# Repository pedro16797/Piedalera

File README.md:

# Piedalera

Firmware for a Raspberry Pi Pico MIDI pedalboard: 20 foot keys, two octave
buttons, a small OLED display and a 5-pin DIN MIDI output. Written in C on
the [Pico SDK](https://github.com/raspberrypi/pico-sdk).

- **Install it:** [setup guide](docs/setup-guide.md)
- **Play it:** [what each pedal does](docs/playing.md)
- **Change settings:** [configuration](docs/configuration.md)

The original MicroPython firmware is kept in [`legacy/`](legacy/) for
reference; this firmware supersedes it.

## Building

Needs the Pico SDK and an `arm-none-eabi` toolchain.

```sh
export PICO_SDK_PATH=/path/to/pico-sdk
cmake -B build -DPICO_BOARD=pico   # or pico_w, pico2, pico2_w
cmake --build build
```

Host tests (any C compiler):

```sh
cmake -S test -B build-test && cmake --build build-test && ctest --test-dir build-test
```

Display preview, rendered with the firmware's own drawing code; open
`build-preview/preview.html` afterwards:

```sh
cmake -S tools/preview -B build-preview
cmake --build build-preview --target preview-run
```

CI builds the firmware and default settings for all four boards on every
push to `master`; tagging `v*` publishes a release.

## Layout

| Path | Contents |
|------|----------|
| `src/` | Firmware ([architecture](docs/architecture.md)) |
| `test/` | Host tests |
| `tools/` | `config2uf2.py` (settings to UF2), `sprites.py` (PNG assets to C), `preview/` |
| `assets/` | Sprites for the splash, config icons and diagrams |
| `config/` | Default settings |
| `hardware/picorgano/` | KiCad board ([hardware](docs/hardware.md)) |
| `legacy/` | Original MicroPython firmware |

Plans are in the [roadmap](docs/roadmap.md).

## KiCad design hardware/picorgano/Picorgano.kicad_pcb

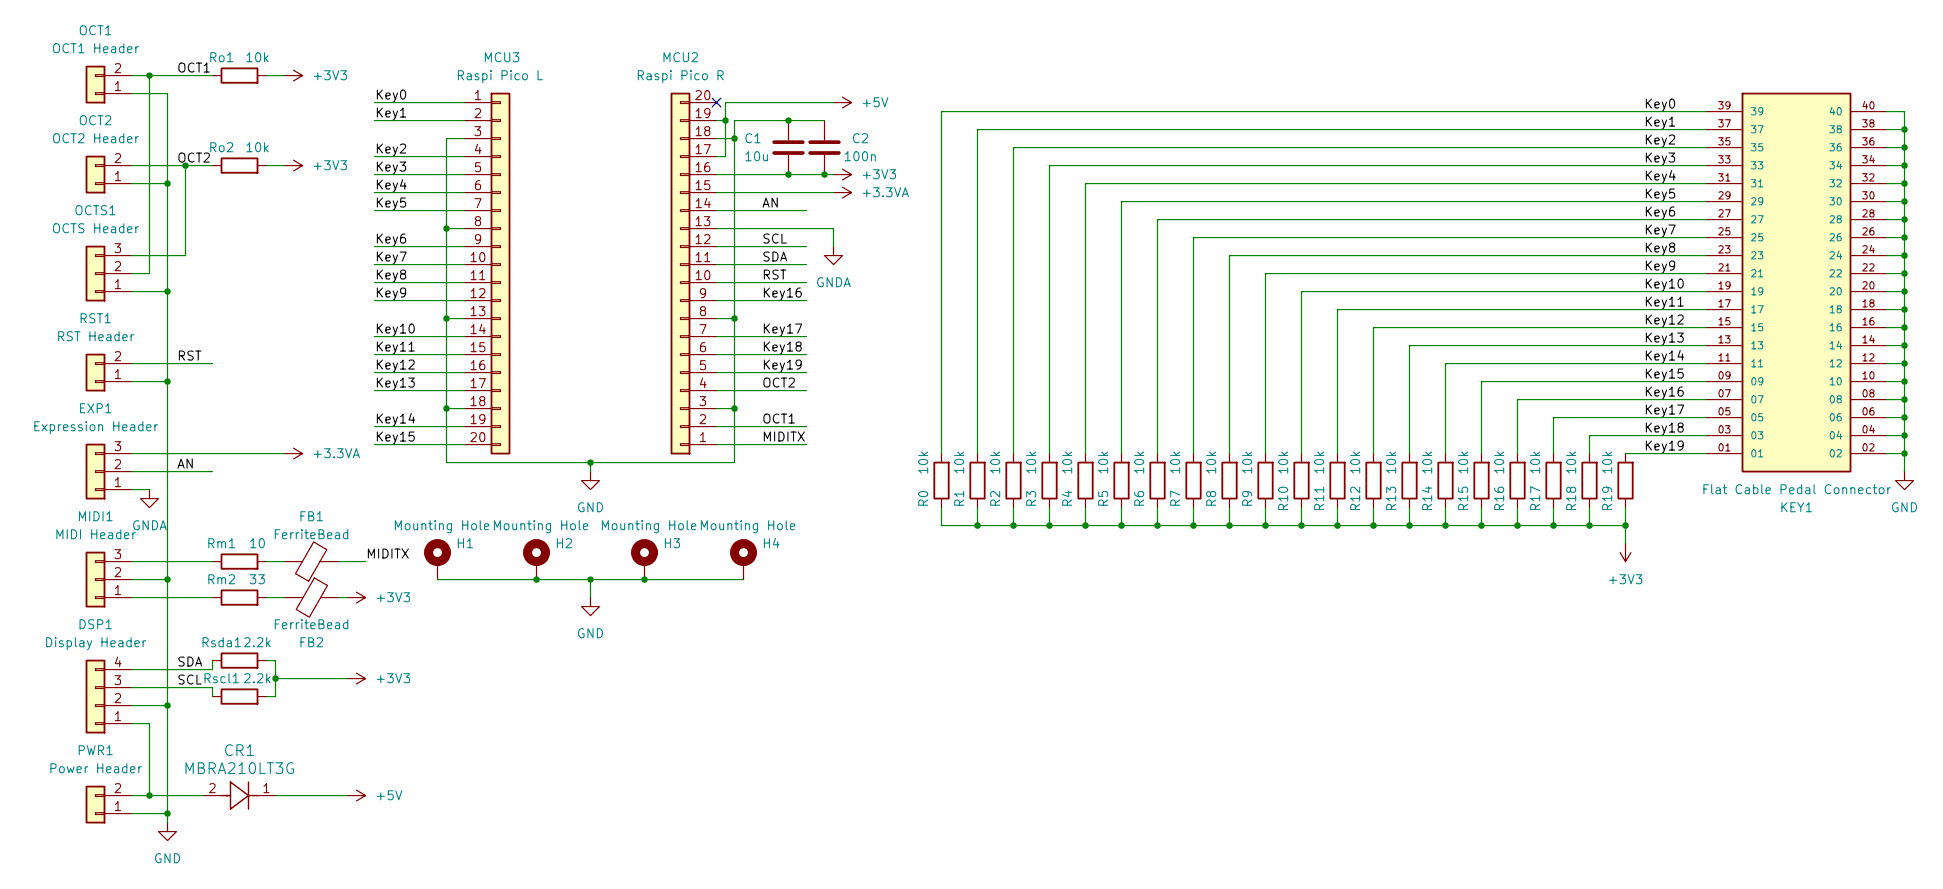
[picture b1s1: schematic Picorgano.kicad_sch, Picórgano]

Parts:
C1: 10u; CP_EIA-3216-10_Kemet-I_Pad1.58x1.35mm_HandSolder
C2: 100n; CP_EIA-3216-10_Kemet-I_Pad1.58x1.35mm_HandSolder
CR1: MBRA210LT3G; DIODE_SMA_4P32X2P6_ONS
DSP1: Display Header; JST_EH_B4B-EH-A_1x04_P2.50mm_Vertical
EXP1: Expression Header; JST_EH_B3B-EH-A_1x03_P2.50mm_Vertical
FB1, FB2: FerriteBead; R_1206_3216Metric
H1, H2, H3, H4: Mounting Hole; MountingHole_2.2mm_M2_DIN965_Pad
KEY1: Flat Cable Pedal Connector; SAMTEC_EHF-120-01-F-D; PARTREV R
MCU2: Raspi Pico R; PinSocket_1x20_P2.54mm_Vertical
MCU3: Raspi Pico L; PinSocket_1x20_P2.54mm_Vertical
MIDI1: MIDI Header; JST_EH_B3B-EH-A_1x03_P2.50mm_Vertical
OCT1: OCT1 Header; JST_EH_B2B-EH-A_1x02_P2.50mm_Vertical
OCT2: OCT2 Header; JST_EH_B2B-EH-A_1x02_P2.50mm_Vertical
OCTS1: OCTS Header; JST_EH_B3B-EH-A_1x03_P2.50mm_Vertical
PWR1: Power Header; JST_EH_B2B-EH-A_1x02_P2.50mm_Vertical
R0, R1, R2, R3, R4, R5, R6, R7, R8, R9, R10, R11, R12, R13, R14, R15, R16, R17, R18, R19: 10k; R_1206_3216Metric_Pad1.30x1.75mm_HandSolder
RST1: RST Header; JST_EH_B2B-EH-A_1x02_P2.50mm_Vertical
Rm1: 10; R_1206_3216Metric_Pad1.30x1.75mm_HandSolder
Rm2: 33; R_1206_3216Metric_Pad1.30x1.75mm_HandSolder
Ro1, Ro2: 10k; R_1206_3216Metric_Pad1.30x1.75mm_HandSolder
Rscl1: 2.2k; R_1206_3216Metric_Pad1.30x1.75mm_HandSolder
Rsda1: 2.2k; R_1206_3216Metric_Pad1.30x1.75mm_HandSolder

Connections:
+3.3VA: EXP1.3, MCU2.15
+3V3: C1.1, C2.1, FB2.1, MCU2.16, R0.1, R1.1, R2.1, R3.1, R4.1, R5.1, R6.1, R7.1, R8.1, R9.1, R10.1, R11.1, R12.1, R13.1, R14.1, R15.1, R16.1, R17.1, R18.1, R19.1, Ro1.2, Ro2.2, Rscl1.2, Rsda1.2
+5V: CR1.1, MCU2.17, MCU2.19
/AN: EXP1.2, MCU2.14
/Key0: KEY1.39, MCU3.1, R0.2
/Key1: KEY1.37, MCU3.2, R1.2
/Key2: KEY1.35, MCU3.4, R2.2
/Key3: KEY1.33, MCU3.5, R3.2
/Key4: KEY1.31, MCU3.6, R4.2
/Key5: KEY1.29, MCU3.7, R5.2
/Key6: KEY1.27, MCU3.9, R6.2
/Key7: KEY1.25, MCU3.10, R7.2
/Key8: KEY1.23, MCU3.11, R8.2
/Key9: KEY1.21, MCU3.12, R9.2
/Key10: KEY1.19, MCU3.14, R10.2
/Key11: KEY1.17, MCU3.15, R11.2
/Key12: KEY1.15, MCU3.16, R12.2
/Key13: KEY1.13, MCU3.17, R13.2
/Key14: KEY1.11, MCU3.19, R14.2
/Key15: KEY1.09, MCU3.20, R15.2
/Key16: KEY1.07, MCU2.9, R16.2
/Key17: KEY1.05, MCU2.7, R17.2
/Key18: KEY1.03, MCU2.6, R18.2
/Key19: KEY1.01, MCU2.5, R19.2
/MIDITX: FB1.2, MCU2.1
/OCT1: MCU2.2, OCT1.2, OCTS1.2, Ro1.1
/OCT2: MCU2.4, OCT2.2, OCTS1.3, Ro2.1
/RST: MCU2.10, RST1.2
/SCL: DSP1.3, MCU2.12, Rscl1.1
/SDA: DSP1.4, MCU2.11, Rsda1.1
GND: C1.2, C2.2, DSP1.2, H1.1, H2.1, H3.1, H4.1, KEY1.02, KEY1.04, KEY1.06, KEY1.08, KEY1.10, KEY1.12, KEY1.14, KEY1.16, KEY1.18, KEY1.20, KEY1.22, KEY1.24, KEY1.26, KEY1.28, KEY1.30, KEY1.32, KEY1.34, KEY1.36, KEY1.38, KEY1.40, MCU2.3, MCU2.8, MCU2.18, MCU3.3, MCU3.8, MCU3.13, MCU3.18, MIDI1.2, OCT1.1, OCT2.1, OCTS1.1, PWR1.1, RST1.1
GNDA: EXP1.1, MCU2.13
unnamed: CR1.2, DSP1.1, PWR1.2
unnamed: FB1.1, Rm1.2
unnamed: FB2.2, Rm2.2
unnamed: MIDI1.1, Rm2.1
unnamed: MIDI1.3, Rm1.1

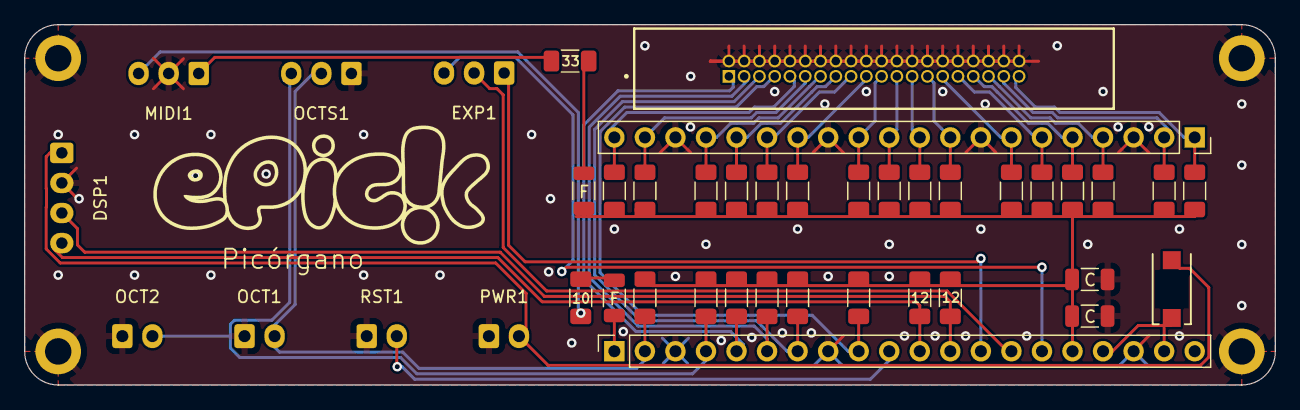
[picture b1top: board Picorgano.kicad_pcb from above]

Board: 2 copper layers, 104.0 x 30.0 mm, 46 parts (0 on the bottom side), 37 nets.
